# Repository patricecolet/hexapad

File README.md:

# HEXAPAD
MIDI USB hexagonal interface made of 7 pads with velocity, aftertouch, and and a distance sensor

### [- Introduction](#Introduction)
### [- Description](#Description)
### [- Schematique](#Schematique)
### [- PCB](#PCB)
### [- Firmware](#Firmware)
### [- Dependences](#Dependences)
### [- MIDI implementation](#implementation)
  
### Introduction

Cet appareil est un hexapad doté de différents capteurs capacitifs qui, lorsqu'ils sont en contract avec des doigts, envoient des signaux ou commandes MIDI à l'aide d'un câble USB vers un ordinateur.
Le MIDI est est un protocole de communication et un format de fichier dédiés à la musique utilisés pour la communication entre instruments électroniques, contrôleurs, séquenceurs, et logiciels de musique.
 
Le microcontrôleur utilisé est un Seeed Studio XIAO SAMD21 qui est programmé avec l'IDE Arduino. Il dispose de 7 entrées capacitives Qtouch qui servent à déclencher des notes de musique, d'un capteur de vibrations piézoélectriques et d'un capteur de proximité infrarouge pour modifier les sons. 

### Description

Nous disposons de 7 broches pour nos capteurs capacitifs qui doivent etre répartie avec la meme surface.

L'idée serait donc une forme hexagonale qui serait divisée en 6 parties, avec un hexagone plus petit au centre.

L'hexagone devra faire 15,5 cm de haut et chaque trapèse doit etre espacé de 2 mm pour éviter les perturbations. C'est a l'aide du logiciel Geogebra que nous avons réussi a trouver les dimensions idéale.

### SCHEMATIQUE 

Voici l'élaborer de la carte électronique qui accueillera nos capteurs capacitifs, le microcontrôleur, le capteur de vibration et le capteur de distance.

Conformément aux recommandations de la documentation technique, nous avons mis en place des résistances de Pull Up  sur chaque broche du capteur de distance (VL53l0X) et nous avons mis des condensateurs de découplage sur AVDD et AVDDVCSEL.

Nous avons également installé des boutons poussoir pour réinitialiser le microcontrôleur et le VL53L0X. Enfin pour le câblage du piezo, nous avons mis une résistance et une diode en parallèle. 

### PCB 

Pour la partie PCB, les composants devaient etre tous groupés pour que la carte ne soit pas trop grande.

Des tests ont étés réalisé aux préalables pour savoir si la longueur des fils/pistes pouvait avoir une influence sur la sensibilité des capteurs. En réalité, plus les pistes sont étendues, plus la variation du signal est faible. C'est pour cette raison que nous devons nous assurer que les pistes soient les moins longues possibles.

Pour éviter toute perturbation, l'hexagone sera recouvert d'un plan de masse qui nous protègera des parasites.

De ce fait il y a moins de charges capacitives entre chaque capteur car elles sont entraînées vers le même potentiel. Il y aura un champ électrique plus fort entre le capteur et l'utilisateur, ce qui augmentera la sensibilité des capteurs.

### Firmware

Le programme est composé de 4 grandes parties :

#### [-Capteur de distance](#distance)
#### [-Capteur Piezoelectrique](#Piezoelectrique)
#### [-Capteur capacitif Qtouch](#Qtouch)
#### [-Message Midi](#Midi)

##### Capteur de distance 

##### Capteur Piezoelectrique

Le capteur piézoélectrique est un capteur de vibration, il va donc nous permettre de détecter l'intensité de nos appuis sur l'hexapad. Nous allons utiliser la fonction TimerCallBack pour faire appel à notre capteur piézo lorsqu'il détectera un changement d'état de sa part. Nous avons choisi de structurer le code du piézo en utilisant un Switch case pour évaluer l'état de notre piezo.

Les doubles rebonds persistaient toujours donc nous avons implanter un seuil glissant qui varirait en fonction de la valeur peak du piézo.

##### Capteur capacitif Qtouch

Les hexapad se déclanche lorsqu'un doigt s'approche d'un capteur capacitif, il va perturbe le champ électrique du pad, ce qui est détecté par l'entrée QTouch. Cela permet au microcontroller de déterminer la surface du toucher et va intéragir avec du son plus ou moins déformer. On va nommé cette deformation l'AfterTouch.

##### Message Midi

## Dependences

* MIDIUSB
* Adafruit_FreeTouch
* Adafruit_VL53L0X
* MovingAverage

## MIDI implémentation

* Destination 1 -> Pad 1
* Destination 2 -> Pad 2
* Destination 3 -> Pad 3
* Destination 4 -> Pad 4
* Destination 5 -> Pad 5
* Destination 6 -> Pad 6
* Destination 7 -> Pad 7
* Destination 8 -> Lidar
* Destination 9 -> Advanced Settings

|STRUCTURE MESSAGE SYSEX|DECHIFFRAGE| Description|
|:---:|:---:|:---:|
|F0|240|Début du message Sysex|
|48|H|Identifiant ASCII|
|45|E|Identifiant ASCII|
|58|X|Identifiant ASCII|
|41|A|Identifiant ASCII|
|50|P|Identifiant ASCII|
|41|A|Identifiant ASCII|
|44|D|Identifiant ASCII|
|30|0|Fin Identifiant ASCII|
|01 ou 02|1(SET) ou 2(GET)|Commande|
|01|1|Version|
|00|0|Révision|
|XX|XX|Destination|
|XX|XX|Numéro de paramètre|
|XX|XX|Valeur|
|F7|247|Fin du message Sysex|

##### Destinataire de 1 à 7
|NUMERO DE PARAMETRE|PADSETTINGS|
|:---:|:---:|
|1|Canal MIDI|
|2|Note MIDI 1|
|3|Seuil 1|
|4|Note MIDI 2|
|5|Seuil 2|
|6|Note MIDI 3|
|7|Seuil 3|
|8|Trig Mode (0 = Percussion, 1 = Keyboard ,2 = Button|
|9|Velocity Curve (0 = Linéaire, 1 = Exponnentielle ,2 = Logarithmique, 3 = Sigmoid)|
|10|AfterTouch Curve (0 = Linéaire, 1 = Exponnentielle ,2 = Logarithmique, 3 = Sigmoid)|
|11|Piezo (1 = Activate, 0 = Disable)|
|12|QTouch (1 = Activate, 0 = Disable)|

#### EXEMPLE MODIFICATION DU TRIG MODE SUR LE PAD 6 DE PADSETTINGS
|||||||||||||DESTINATION|PARAMETRE|VALEUR||
|:---:|:---:|:---:|:---:|:---:|:---:|:---:|:---:|:---:|:---:|:---:|:---:|:---:|:---:|:---:|:---:|
|F0|48|45|58|41|50|41|44|30|01|01|00|06|08|02|F7|
|240|H|E|X|A|P|A|D|0|1|1|0|6|8|2|247|

##### Destination 8
|NUMERO DE PARAMETRE|LIDAR|
|:---:|:---:|
|1|Canal MIDI|
|2|Note MIDI|
|3|Courbe (0 = Linéaire, 1 = Exponnentielle ,2 = Logarithmique, 3 = Sigmoid)|
|4|Low Threshold LSB|
|5|Low Threshold MSB|
|6|High Threshold LSB|
|7|High Threshold MSB|
|8|Controller LSB|
|9|Controller MSB|
|10|Scale|
|11|Scale Low Range|
|12|Scale High Range|
|13|Lidar (1 = Activate, 0 = Disable)|

#### EXEMPLE MODIFICATION DU LOW THRESHOLD MSB SUR LE LIDAR
|||||||||||||DESTINATION|PARAMETRE|VALEUR||
|:---:|:---:|:---:|:---:|:---:|:---:|:---:|:---:|:---:|:---:|:---:|:---:|:---:|:---:|:---:|:---:|
|F0|48|45|58|41|50|41|44|30|01|01|00|08|05|7F|F7|
|240|H|E|X|A|P|A|D|0|1|1|0|8|5|127|247|

##### Destination 9
|NUMERO DE PARAMETRE|ADVANCED SETTINGS|
|:---:|:---:|
|1|Piezo Threshold LSB|
|2|Piezo Threshold MSB|
|3|Piezo Sensitivity LSB|
|4|Piezo Sensitivity MSB|
|5|Debounce Time LSB|
|6|Debounce Time MSB|
|7|QTouch RoundOff|

#### EXEMPLE MODIFICATION DU ROUNDOFF DANS ADVANCED SETTINGS
|||||||||||||DESTINATION|PARAMETRE|VALEUR||
|:---:|:---:|:---:|:---:|:---:|:---:|:---:|:---:|:---:|:---:|:---:|:---:|:---:|:---:|:---:|:---:|
|F0|48|45|58|41|50|41|44|30|01|01|00|09|07|0F|F7|
|240|H|E|X|A|P|A|D|0|1|1|0|9|7|15|247|

#TODO

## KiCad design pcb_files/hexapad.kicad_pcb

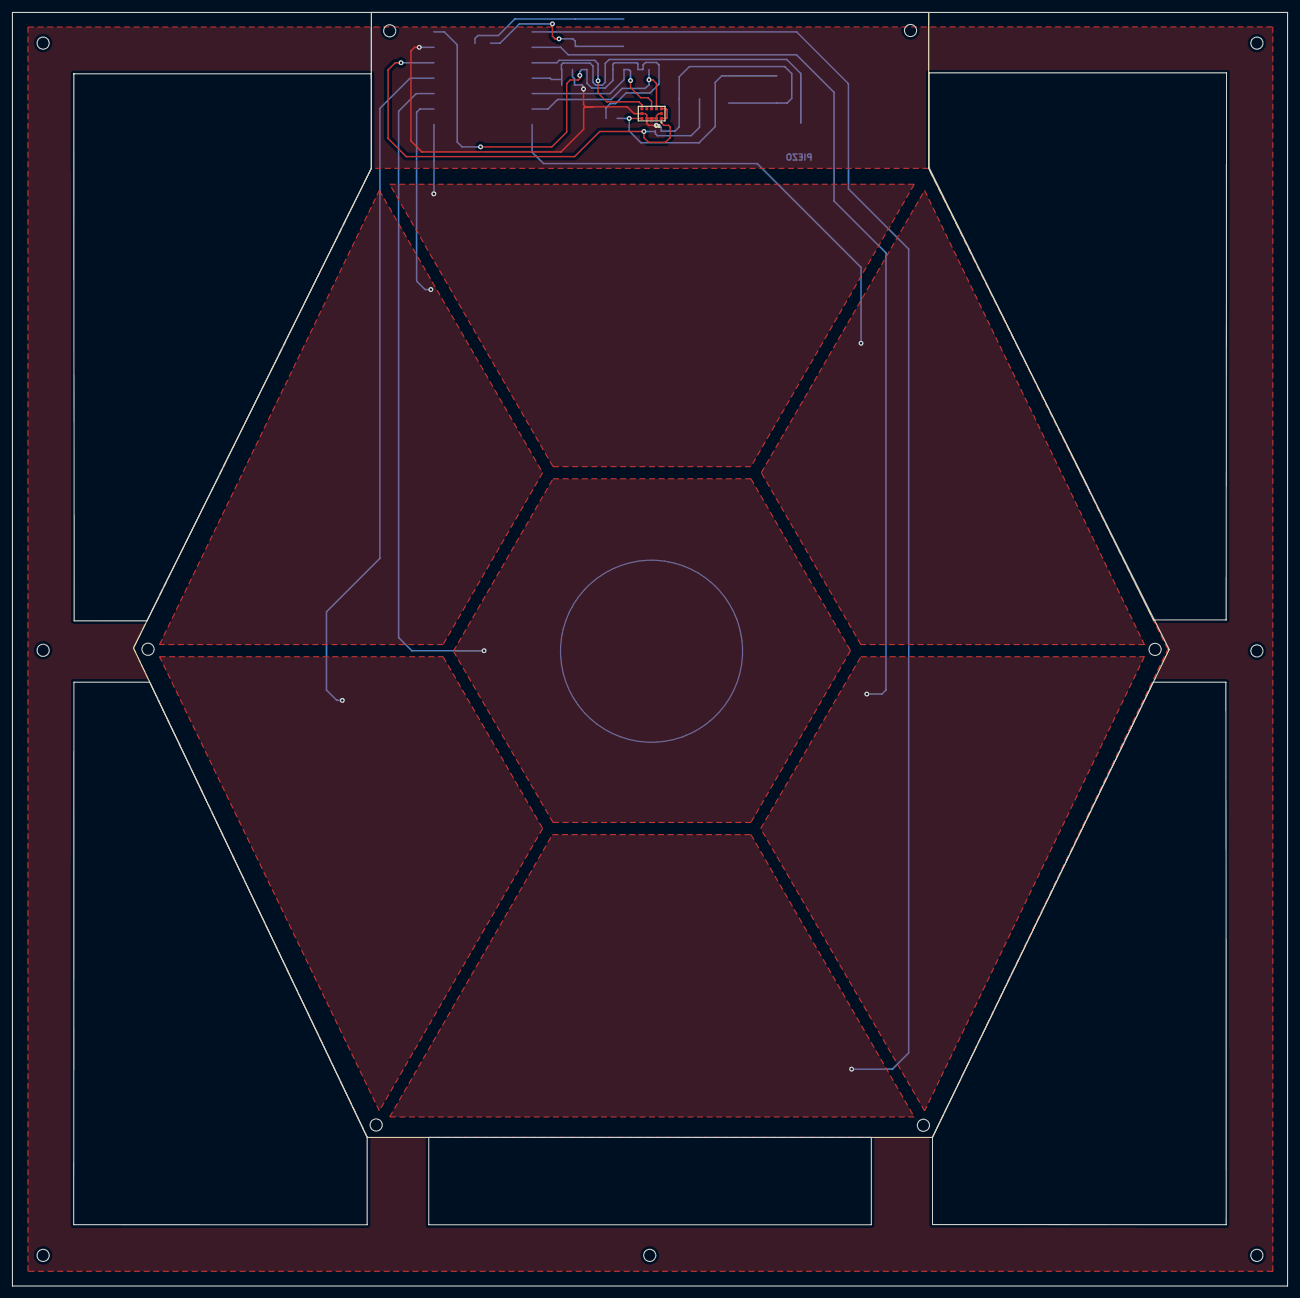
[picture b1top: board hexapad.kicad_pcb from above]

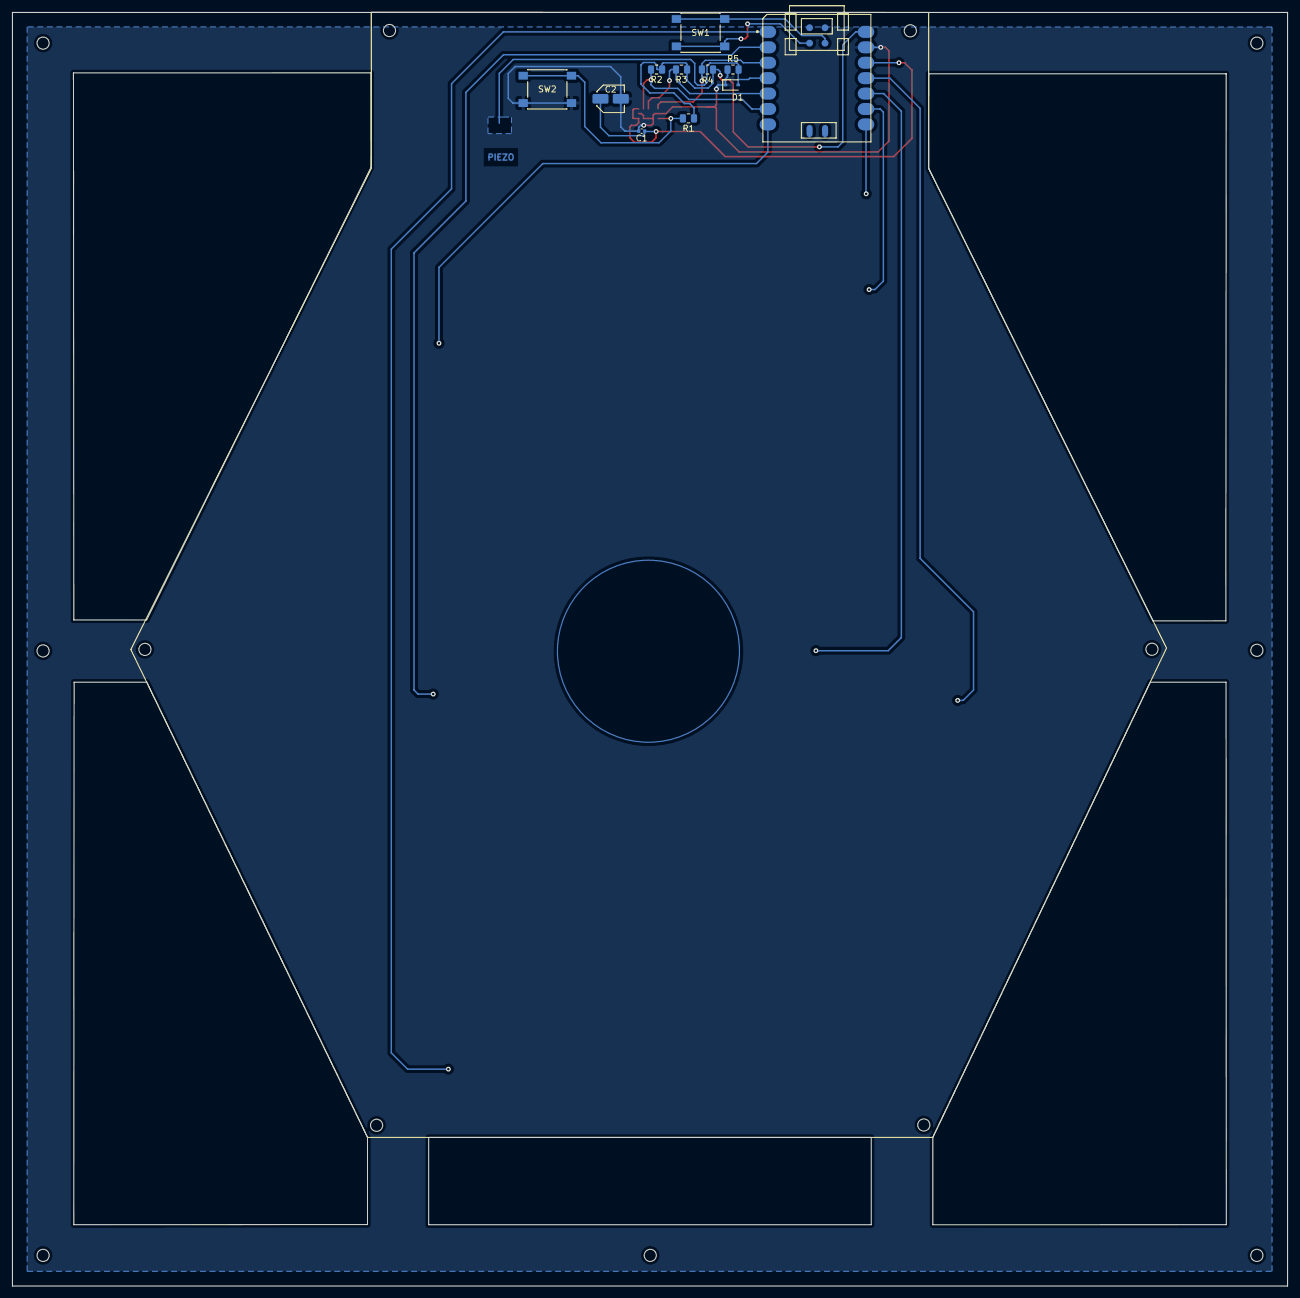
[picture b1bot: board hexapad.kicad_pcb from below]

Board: 2 copper layers, 210.0 x 209.7 mm, 12 parts (11 on the bottom side), 9 nets.

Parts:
C1: 100nF; C_0402_1005Metric
C2: 4.7uF; C_Elec_4x5.4
D1: DIODE; D_SOD-323
R1, R2, R3, R4: 2K; R_0805_2012Metric
R5: 20K; R_0805_2012Metric
SW1, SW2: SW_Push; SW_Push_1P1T_NO_6x6mm_H9.5mm
U1: SeeeduinoXIAO; Seeeduino XIAO-MOUDLE14P-2.54-21X17.8MM
U2: VL53L0X; SENSOR_VL53L0X

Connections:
+5V: R1.1, R2.1, R3.1, R4.1, U1.14 (5V)
GND: C1.2, C2.2, D1.1 (A), R5.2, SW2.2, U1.13 (GND), U2.2 (AVSSVCSEL), U2.3 (GND), U2.4 (GND), U2.6 (GND), U2.12 (GND)
unnamed: C1.1, C2.1, U1.12 (3V3), U2.1 (AVDDVCSEL), U2.11 (AVDD)
unnamed: R1.2, SW2.1, U2.5 (~XSHUT)
unnamed: R2.2, U1.6 (PA9_A5_D5_SCL), U2.10 (SCL)
unnamed: R3.2, U1.5 (PA8_A4_D4_SDA), U2.9 (SDA)
unnamed: R4.2, U1.3 (PA10_A2_D2), U2.7 (GPIO1)
unnamed: SW1.1, U1.19 (RESET)
unnamed: SW1.2, U1.20 (GND)

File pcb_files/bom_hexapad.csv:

"Id";"Designator";"Package";"Quantity";"Designation";"Supplier and ref";
1;"U2";"SENSOR_VL53L0X";1;"VL53L0X";;;
2;"R3,R2,R4,R1";"R_0805_2012Metric";4;"2K";;;
3;"R5";"R_0805_2012Metric";1;"20K";;;
4;"C2";"C_Elec_4x5.4";1;"4.7uF";;;
5;"SW2,SW1";"SW_Push_1P1T_NO_6x6mm_H9.5mm";2;"SW_Push";;;
6;"D1";"D_SOD-323";1;"DIODE";;;
7;"C1";"C_0402_1005Metric";1;"100nF";;;
8;"U1";"Seeeduino XIAO-MOUDLE14P-2.54-21X17.8MM";1;"SeeeduinoXIAO";;;

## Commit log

2023-09-09 added Distance range status to hexapad.h
2023-09-09 redesign README
2023-09-09 added midimap.h
2023-09-09 added pad trig mode
2023-09-10 refactoring qtouch.hpp without #define
2024-03-13 update 2024
2024-03-19 set note and channel with pad settings
2024-03-20 uses padsettings structure in midi functions
2024-03-20 added midimessage class
2024-03-20 moved all midi send functions to midiMessage class
2024-03-21 mode boutton
2024-03-22 maj mode boutton
2024-03-22 mode button bool
2024-03-22 mode button fonctionelle sans aftertouch
2024-03-26 curve mode fonctionnel
2024-03-27 Documentation readme sans image
2024-03-27 documentation avec image
2024-03-27 documentation readme avec image
2024-03-27 image
2024-03-28 Sommaire
2024-03-29 essaie piezo disable
2024-03-29 Debut commentaire du code
2024-03-29 Update README.md
    midi implémentation todo et dépendances à la fin du README et ajoutés au sommaire
2024-03-29 images
2024-03-29 images fonctionnel
2024-03-29 upgrade sommaire
2024-03-29 ameilloration text
2024-04-03 midi message update
2024-04-04 update main
2024-04-04 update midi message
2024-04-05 debbuging
2024-04-05 kicad pd projet
2024-04-08 probleme velocity
2024-04-08 probleme piezo
2024-04-09 nouvelle velocity et debug
2024-04-09 advenced settings
2024-04-09 Canal 4 Advenced settings
2024-04-10 firmware
2024-04-11 Advanced settings
2024-04-11 Imgae piezo
2024-04-11 machine a état piezo
2024-04-11 machine a etat piezo
2024-04-11 Advanced settings operationnel
2024-04-11 removed sendNote from piezo class, added debug level, velocity doesn't go to previous value anymore
2024-04-12 correction
2024-04-12 image piezo
2024-04-12 allure piezo
2024-04-15 reglage pb velocity
2024-04-16 renamed hexapad to pcb_files, added jsfx editor file
2024-04-16 moved midi fn to midiMessage class
2024-04-17 mise en place du sysex
2024-04-17 suppression d un dosssier en doublon
2024-04-17 updated editor
2024-04-17 reglage debounce time et debut de l'implémentation du controller 0
2024-04-17 modif image piezo
2024-04-17 test
2024-04-18 implementation de l'envoie du buffer
2024-04-18 mise en place du DEBUG pour les messages dans midimessage
2024-04-18 debut commentaire code
2024-04-18 Premier commit
2024-04-19 Premier test de la mise en place des differente note selon le qtouch et modification du ReadMe
2024-04-19 added all menu
2024-04-19 supression de la 4eme note
2024-04-19 correction code + debut developpement Readme
2024-04-19 correction erreur
2024-04-26 commencement implémentation du capteur de distance dans midimessage
2024-04-26 ajout aftetouch
2024-04-29 ajout mode button et mode Keyboard sur le capteur de distance
2024-04-29 added sysex class
2024-04-29 deplacement de AfterTouchNote et VelocityCurve de Midimessage a Hexapad.h
2024-04-30 adding sysex class
2024-05-02 refactoring
2024-05-02 Rebasage de la fonction AfterTouchNote
2024-05-02 mise a jour Readme
2024-05-02 Structure des messages Sysex
2024-05-02 removed sendMidi()
2024-05-03 Structures messages Sysex
2024-05-03 Exemple structure Syesx
2024-05-03 Exemple message Sysex
2024-05-03 sysex
2024-05-03 image hexapad géogébra
2024-05-03 image hexagone géogébra
2024-05-03 Modification explication sysex
2024-05-03 Modification Message Sysex
2024-05-03 modification mise en forme du texte
2024-05-03 modification de la mise en forme du texte
2024-05-03 modification readme
2024-05-03 DEGUB
2024-12-18 update pcb and sysex
2025-02-15 added pd exemple, removed timing variables
2025-02-16 added pd sysex saving into file
